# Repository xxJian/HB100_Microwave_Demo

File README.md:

# HB100_Microwave_Demo

This is a KiCad project. At first it is created with KiCad v4. However my PC has installed KiCad v5 and this project was converted to a project of KiCad v5. I am not sure whether there is any problem with KiCad v4 when opening these files.

Dimension of HB100 module can be found in HB100_Microwave_Sensor_Module_Datasheet(1).pdf.
Application circuit can be found in HB100_Microwave_Sensor_Application_Note.pdf.

And it also was verified by me, as you can see in the jpg files. 

There is one tiny problem with my board. The retangular cutoff does not fit with HB100. This board functions well, but is not so pretty. And the distance has not been tested yet.

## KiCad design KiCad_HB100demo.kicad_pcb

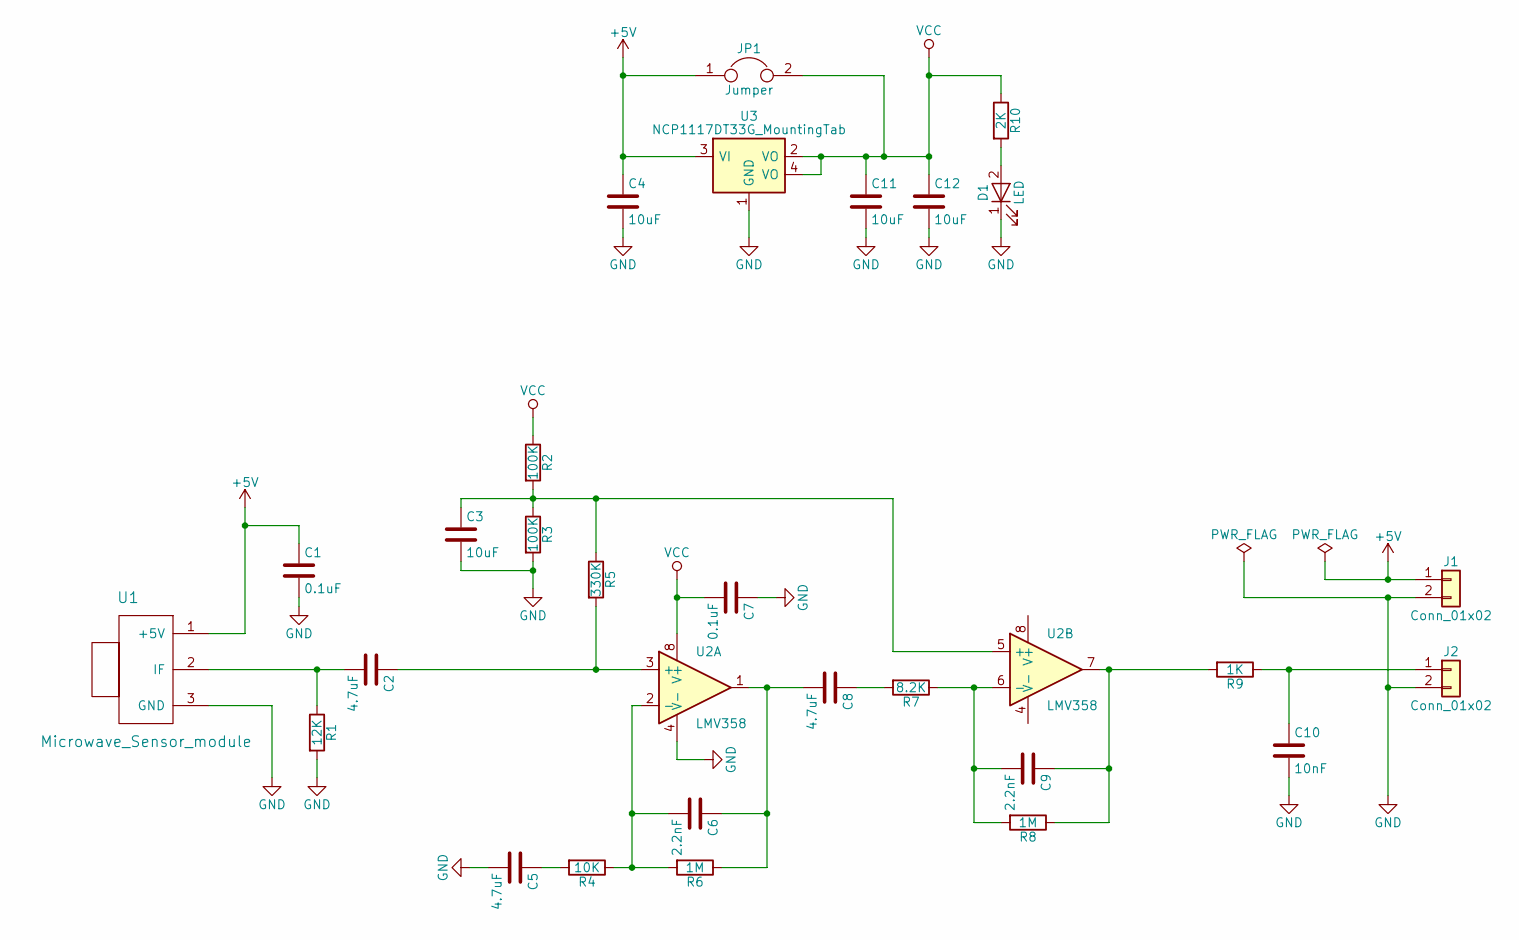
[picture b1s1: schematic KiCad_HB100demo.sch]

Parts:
C1, C7: 0.1uF; C_0805_HS
C2: 4.7uF; C_0805_HS
C3, C4, C11, C12: 10uF; C_1206_HS
C5, C8: 4.7uF; C_1206_HS
C6, C9: 2.2nF; C_0805_HS
C10: 10nF; C_0805_HS
D1: LED; LED_0805_HS
J1, J2: Conn_01x02; Pin_Header_Straight_1x02_Pitch2.54mm
JP1: Jumper; Pin_Header_Straight_1x02_Pitch2.54mm
R1: 12K; R_0805_HS
R2, R3: 100K; R_0805_HS
R4: 10K; R_0805_HS
R5: 330K; R_0805_HS
R6, R8: 1M; R_0805_HS
R7: 8.2K; R_0805_HS
R9: 1K; R_0805_HS
R10: 2K; R_0805_HS
U1: Microwave_Sensor_module; HB100
U2: LMV358; SOIC-8_3.9x4.9mm_Pitch1.27mm_HS
U3: NCP1117DT33G_MountingTab; SOT-223_HS

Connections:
+5V: C1.1, C4.1, J1.1, JP1.1, U1.1 (+5V), U3.3 (VI)
GND: C1.2, C3.2, C4.2, C5.2, C7.1, C10.2, C11.2, C12.2, D1.1 (K), J1.2, J2.2, R1.2, R3.2, U1.3 (GND), U2.4 (V-), U3.1 (GND)
unnamed: C2.1, R5.2, U2.3 (+)
unnamed: C2.2, R1.1, U1.2 (IF)
unnamed: C3.1, R2.2, R3.1, R5.1, U2.5 (+)
unnamed: C5.1, R4.2
unnamed: C6.1, C8.2, R6.1, U2.1
unnamed: C6.2, R4.1, R6.2, U2.2 (-)
unnamed: C8.1, R7.2
unnamed: C9.1, R8.1, R9.2, U2.7
unnamed: C9.2, R7.1, R8.2, U2.6 (-)
unnamed: C10.1, J2.1, R9.1
unnamed: D1.2 (A), R10.2
VCC: C7.2, C11.1, C12.1, JP1.2, R2.1, R10.1, U2.8 (V+), U3.2 (VO), U3.4 (VO)

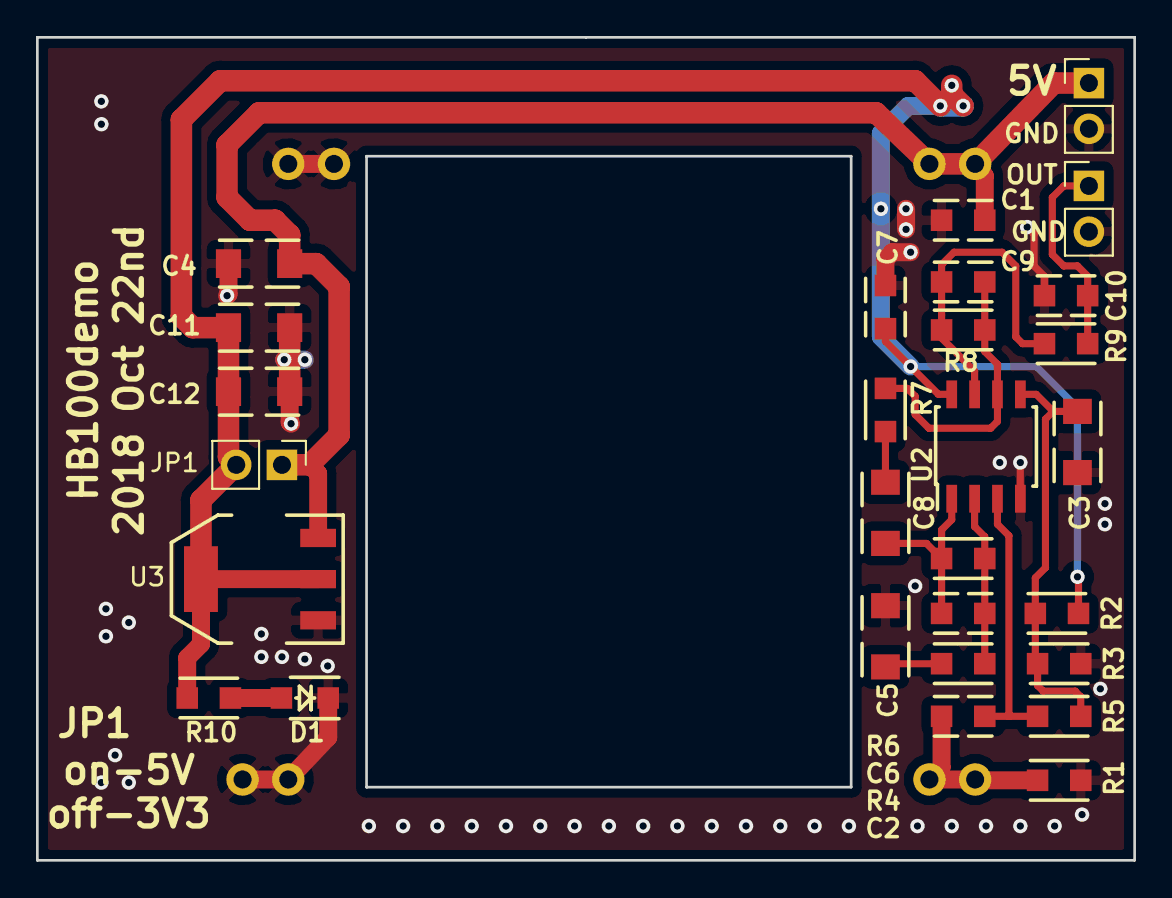
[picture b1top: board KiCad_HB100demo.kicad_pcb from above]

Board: 2 copper layers, 61.0 x 45.7 mm, 29 parts (1 on the bottom side), 14 nets.

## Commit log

2018-10-29 Create 1
